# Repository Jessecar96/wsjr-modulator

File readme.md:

# The Weather STAR Revamped

This project is an update to https://github.com/thetechknight/wsjr-modulator that replaces the Arduino Mega, with a Reaspberry Pi Zero. This allows you to write a data sending solution on device instead of requiring a connection to another computer or server for data.

The `schematic` folder contains the updated schematic and board layout files in KiCad 8. 
`schematic_orig` contains thetechknight's original EAGLE cad schematic.
`code` contains code written for the Arduino based board written for  BASCOM-AVR.

The software that runs on the Raspberry Pi can be found here: https://github.com/Jessecar96/wsjr-data-encoder

License: https://creativecommons.org/licenses/by-nc-sa/4.0/

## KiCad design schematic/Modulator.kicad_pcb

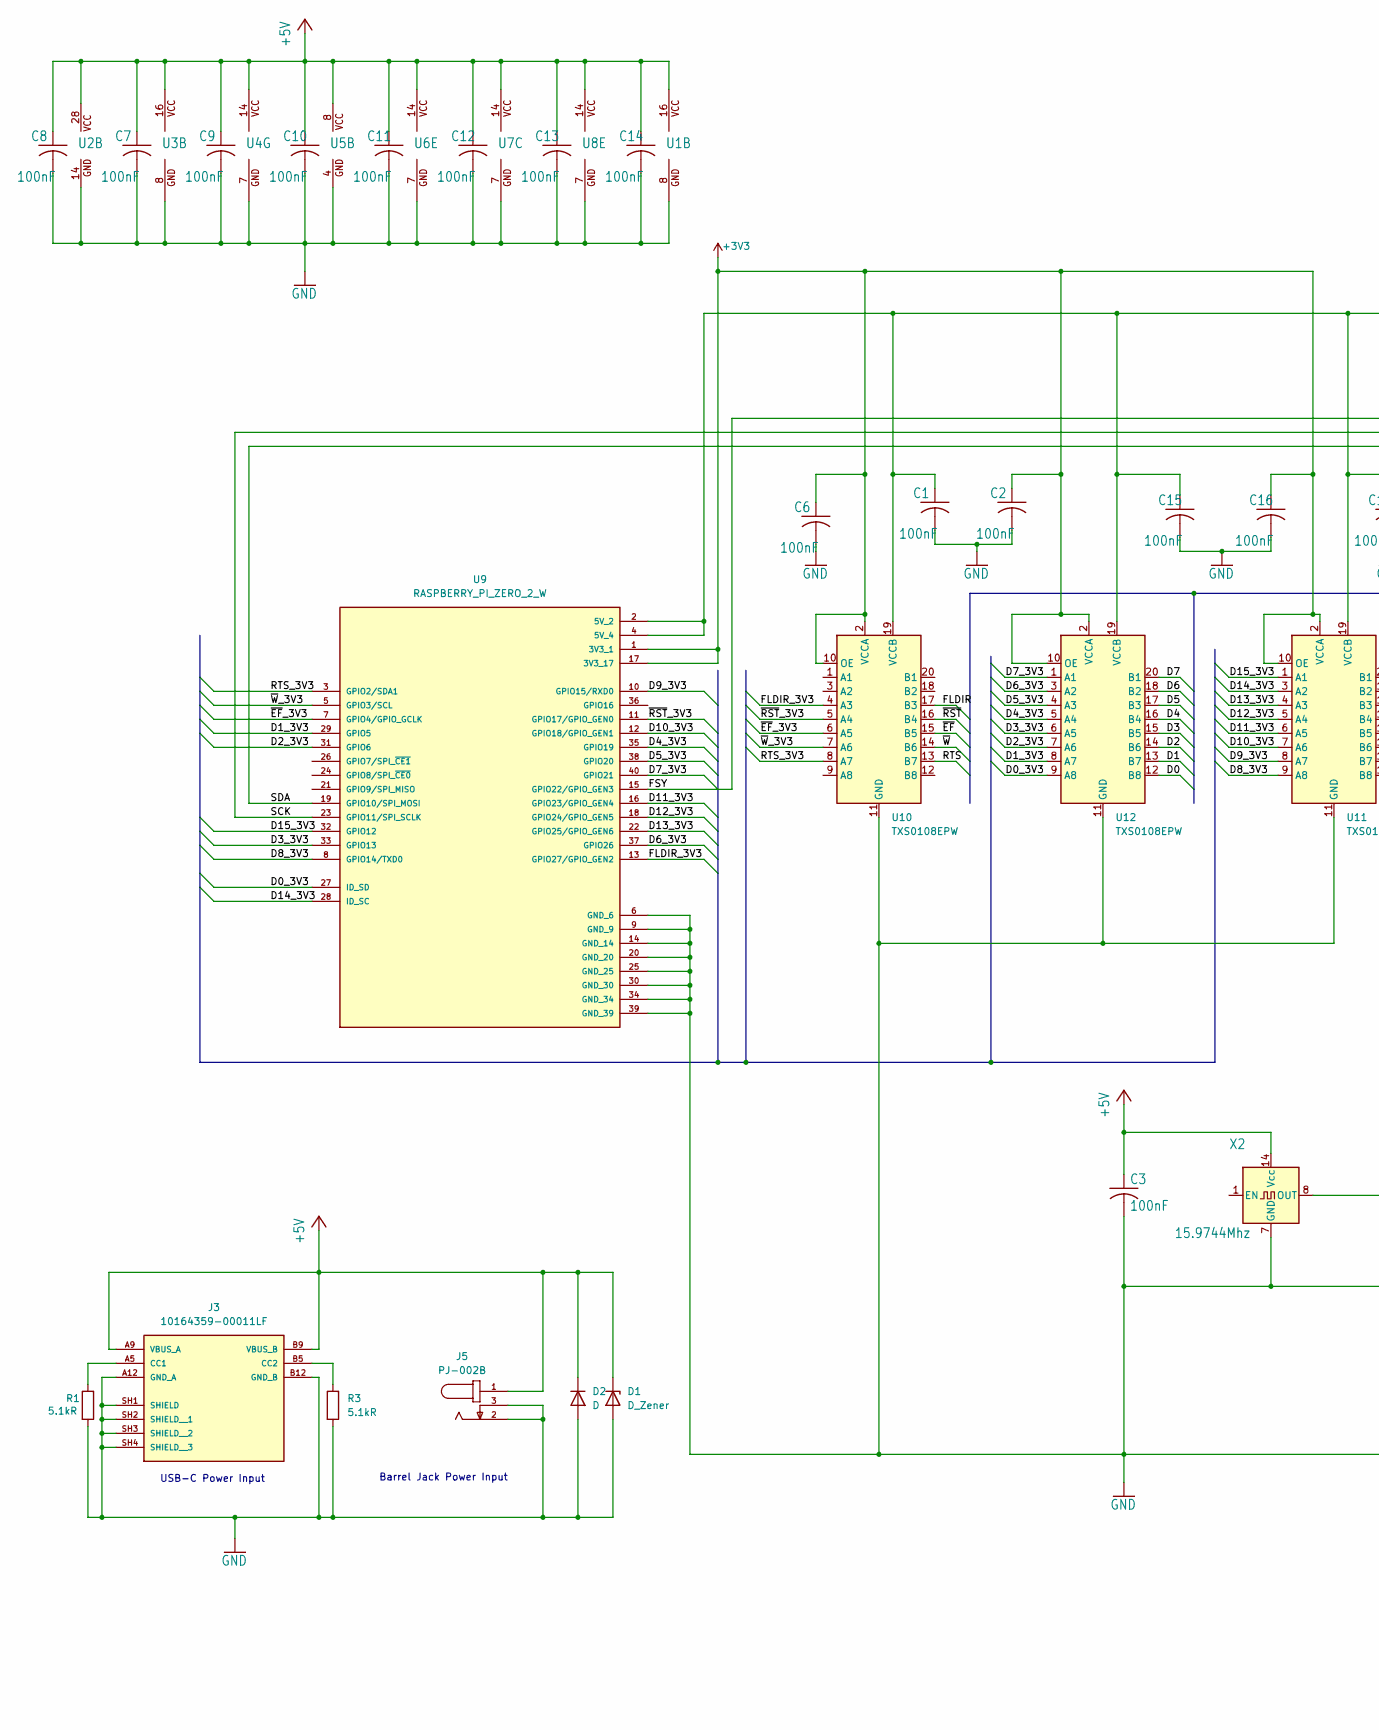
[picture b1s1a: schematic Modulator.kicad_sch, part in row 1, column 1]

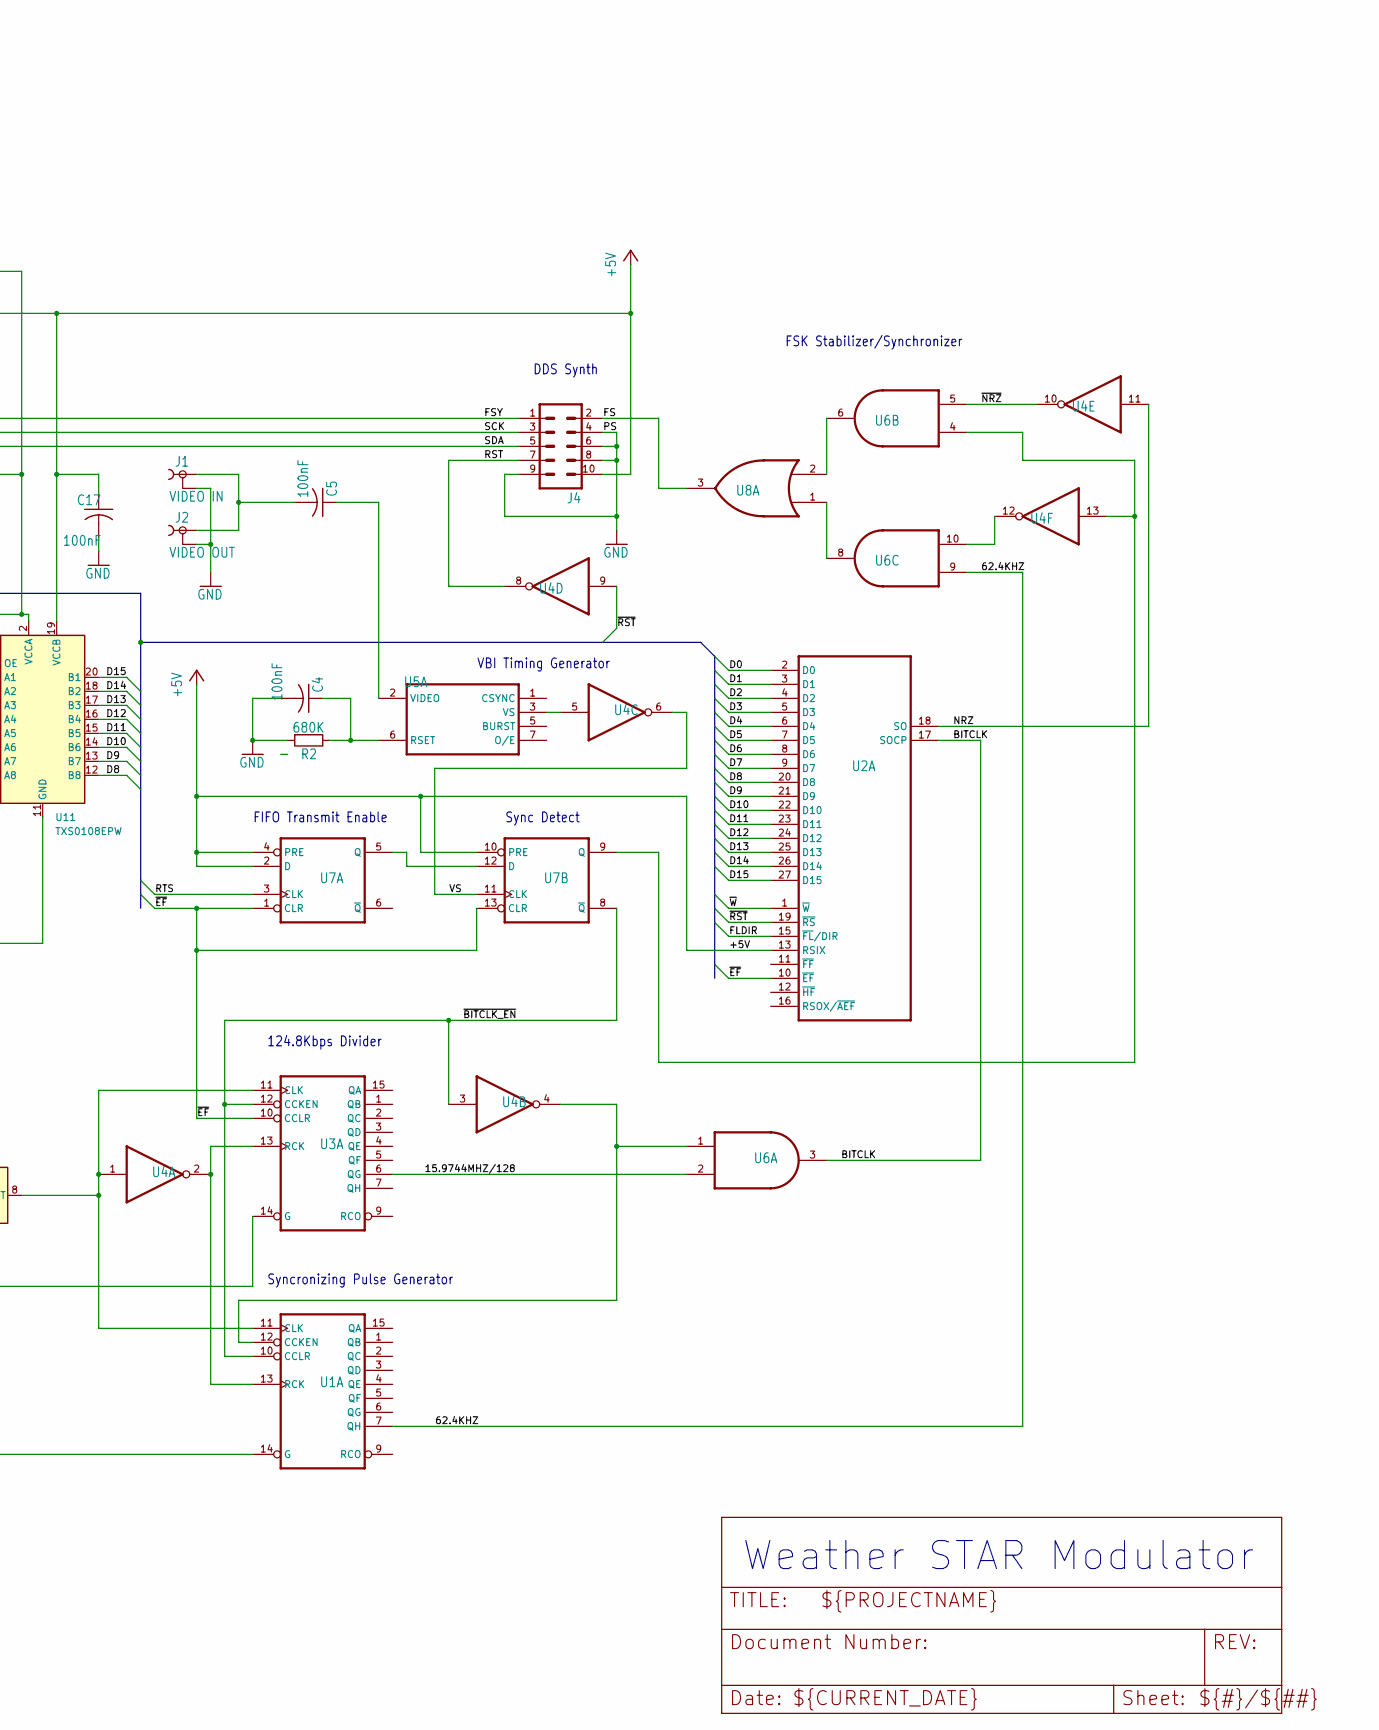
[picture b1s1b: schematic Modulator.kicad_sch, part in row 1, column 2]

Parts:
C1, C2, C6, C15, C16, C17: 100nF; C_0805_2012Metric_Pad1.18x1.45mm_HandSolder
C3, C4, C5, C7, C8, C9, C10, C11, C12, C13, C14: 100nF; C_Disc_D4.7mm_W2.5mm_P5.00mm
D1: D_Zener; D_DO-41_SOD81_P7.62mm_Horizontal
D2: D; D_DO-41_SOD81_P7.62mm_Horizontal
J1: VIDEO IN; TOBU3
J2: VIDEO OUT; TOBU3
J3: 10164359-00011LF; AMPHENOL_10164359-00011LF; PARTREV A
J4: MA05-2; AD9834
J5: PJ-002B; CUI_PJ-002B
R1, R3: 5.1kR; R_0805_2012Metric_Pad1.20x1.40mm_HandSolder
R2: 680K; R_Axial_DIN0207_L6.3mm_D2.5mm_P10.16mm_Horizontal
U1, U3: 74590N; DIL16
U2: IDT72125; DIP-28_W7.62mm_LongPads
U4: 7404N; DIL14
U5: LM1881N; DIL08
U6: 7408N; DIL14
U7: 7474N; DIL14
U8: 7432N; DIL14
U9: RASPBERRY_PI_ZERO_2_W; MODULE_RASPBERRY_PI_ZERO_2_W; PARTREV April 2024
U10, U11, U12: TXS0108EPW; TSSOP-20_4.4x6.5mm_P0.65mm
X2: 15.9744Mhz; Oscillator_DIP-14

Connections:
+3V3: C2.1, C6.1, C16.1, U9.1 (3V3_1), U9.17 (3V3_17), U10.2 (VCCA), U10.10 (OE), U11.2 (VCCA), U11.10 (OE), U12.2 (VCCA), U12.10 (OE)
+5V: C1.1, C3.1, C7.1, C8.1, C9.1, C10.1, C11.1, C12.1, C13.1, C14.1, C15.1, C17.1, D1.1 (K), D2.1 (K), J3.A9 (VBUS_A), J3.B9 (VBUS_B), J4.10, J5.1, U1.16 (VCC), U2.13 (RSIX), U2.28 (VCC), U3.16 (VCC), U4.14 (VCC), U5.8 (VCC), U6.14 (VCC), U7.2 (D), U7.4 (PRE), U7.10 (PRE), U7.14 (VCC), U8.14 (VCC), U9.2 (5V_2), U9.4 (5V_4), U10.19 (VCCB), U11.19 (VCCB), U12.19 (VCCB), X2.14 (Vcc)
/15.9744MHZ/128: U3.6 (QG), U6.2 (I1)
/62.4KHZ: U1.7 (QH), U6.9 (I0)
/BITCLK: U2.17 (SOCP), U6.3 (O)
/D0: U2.2 (D0), U12.12 (B8)
/D0_3V3: U9.27 (ID_SD), U12.9 (A8)
/D1: U2.3 (D1), U12.13 (B7)
/D1_3V3: U9.29 (GPIO5), U12.8 (A7)
/D2: U2.4 (D2), U12.14 (B6)
/D2_3V3: U9.31 (GPIO6), U12.7 (A6)
/D3: U2.5 (D3), U12.15 (B5)
/D3_3V3: U9.33 (GPIO13), U12.6 (A5)
/D4: U2.6 (D4), U12.16 (B4)
/D4_3V3: U9.35 (GPIO19), U12.5 (A4)
/D5: U2.7 (D5), U12.17 (B3)
/D5_3V3: U9.38 (GPIO20), U12.4 (A3)
/D6: U2.8 (D6), U12.18 (B2)
/D6_3V3: U9.37 (GPIO26), U12.3 (A2)
/D7: U2.9 (D7), U12.20 (B1)
/D7_3V3: U9.40 (GPIO21), U12.1 (A1)
/D8: U2.20 (D8), U11.12 (B8)
/D8_3V3: U9.8 (GPIO14/TXD0), U11.9 (A8)
/D9: U2.21 (D9), U11.13 (B7)
/D9_3V3: U9.10 (GPIO15/RXD0), U11.8 (A7)
/D10: U2.22 (D10), U11.14 (B6)
/D10_3V3: U9.12 (GPIO18/GPIO_GEN1), U11.7 (A6)
/D11: U2.23 (D11), U11.15 (B5)
/D11_3V3: U9.16 (GPIO23/GPIO_GEN4), U11.6 (A5)
/D12: U2.24 (D12), U11.16 (B4)
/D12_3V3: U9.18 (GPIO24/GPIO_GEN5), U11.5 (A4)
/D13: U2.25 (D13), U11.17 (B3)
/D13_3V3: U9.22 (GPIO25/GPIO_GEN6), U11.4 (A3)
/D14: U2.26 (D14), U11.18 (B2)
/D14_3V3: U9.28 (ID_SC), U11.3 (A2)
/D15: U2.27 (D15), U11.20 (B1)
/D15_3V3: U9.32 (GPIO12), U11.1 (A1)
/FLDIR: U2.15 (~FL/DIR), U10.17 (B3)
/FLDIR_3V3: U9.13 (GPIO27/GPIO_GEN2), U10.4 (A3)
/FS: J4.2, U8.3 (O)
/FSY: J4.1, U9.15 (GPIO22/GPIO_GEN3)
/NRZ: U2.18 (SO), U4.11 (I)
/RST: J4.7, U4.8 (O)
/RTS: U7.3 (CLK), U10.13 (B7)
/RTS_3V3: U9.3 (GPIO2/SDA1), U10.8 (A7)
/SCK: J4.3, U9.23 (GPIO11/SPI_SCLK)
/SDA: J4.5, U9.19 (GPIO10/SPI_MOSI)
/VS: U4.6 (O), U7.11 (CLK)
/~BITCLK_EN: U1.10 (CCLR), U3.12 (CCKEN), U4.3 (I), U7.8 (~Q)
/~EF: U2.10 (~EF), U3.10 (CCLR), U7.1 (CLR), U7.13 (CLR), U10.15 (B5)
/~EF_3V3: U9.7 (GPIO4/GPIO_GCLK), U10.6 (A5)
/~NRZ: U4.10 (O), U6.5 (I1)
/~RST: U2.19 (~RS), U4.9 (I), U10.16 (B4)
/~RST_3V3: U9.11 (GPIO17/GPIO_GEN0), U10.5 (A4)
/~W: U2.1 (~W), U10.14 (B6)
/~W_3V3: U9.5 (GPIO3/SCL), U10.7 (A6)
GND: C1.2, C2.2, C3.2, C4.2, C6.2, C7.2, C8.2, C9.2, C10.2, C11.2, C12.2, C13.2, C14.2, C15.2, C16.2, C17.2, D1.2 (A), D2.2 (A), J1.2, J1.2@1 (2), J1.2@2 (2), J2.2, J2.2@1 (2), J2.2@2 (2), J3.A12 (GND_A), J3.B12 (GND_B), J3.SH1 (SHIELD), J3.SH2 (SHIELD__1), J3.SH3 (SHIELD__2), J3.SH4 (SHIELD__3), J4.4, J4.6, J4.8, J4.9, J5.2, J5.3, R1.2, R2.2, R3.2, U1.8 (GND), U1.14 (G), U2.14 (GND), U3.8 (GND), U3.14 (G), U4.7 (GND), U5.4 (GND), U6.7 (GND), U7.7 (GND), U8.7 (GND), U9.6 (GND_6), U9.9 (GND_9), U9.14 (GND_14), U9.20 (GND_20), U9.25 (GND_25), U9.30 (GND_30), U9.34 (GND_34), U9.39 (GND_39), U10.11 (GND), U11.11 (GND), U12.11 (GND), X2.7 (GND)
unnamed: C5.2, J1.1, J2.1
unnamed: J3.A5 (CC1), R1.1
unnamed: J3.B5 (CC2), R3.1
unnamed: U1.12 (CCKEN), U4.4 (O), U6.1 (I0)
unnamed: U1.11 (CLK), U3.11 (CLK), U4.1 (I), X2.8 (OUT)
unnamed: U1.13 (RCK), U3.13 (RCK), U4.2 (O)
unnamed: U4.5 (I), U5.3 (VS)
unnamed: U4.13 (I), U6.4 (I0), U7.9 (Q)
unnamed: U4.12 (O), U6.10 (I1)
unnamed: C4.1, R2.1, U5.6 (RSET)
unnamed: C5.1, U5.2 (VIDEO)
unnamed: U6.6 (O), U8.2 (I1)
unnamed: U6.8 (O), U8.1 (I0)
unnamed: U7.5 (Q), U7.12 (D)

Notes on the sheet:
DDS Synth
VBI Timing Generator
USB-C Power Input
FSK Stabilizer/Synchronizer
Weather STAR Modulator
FIFO Transmit Enable
Sync Detect
Barrel Jack Power Input
124.8Kbps Divider
Syncronizing Pulse Generator

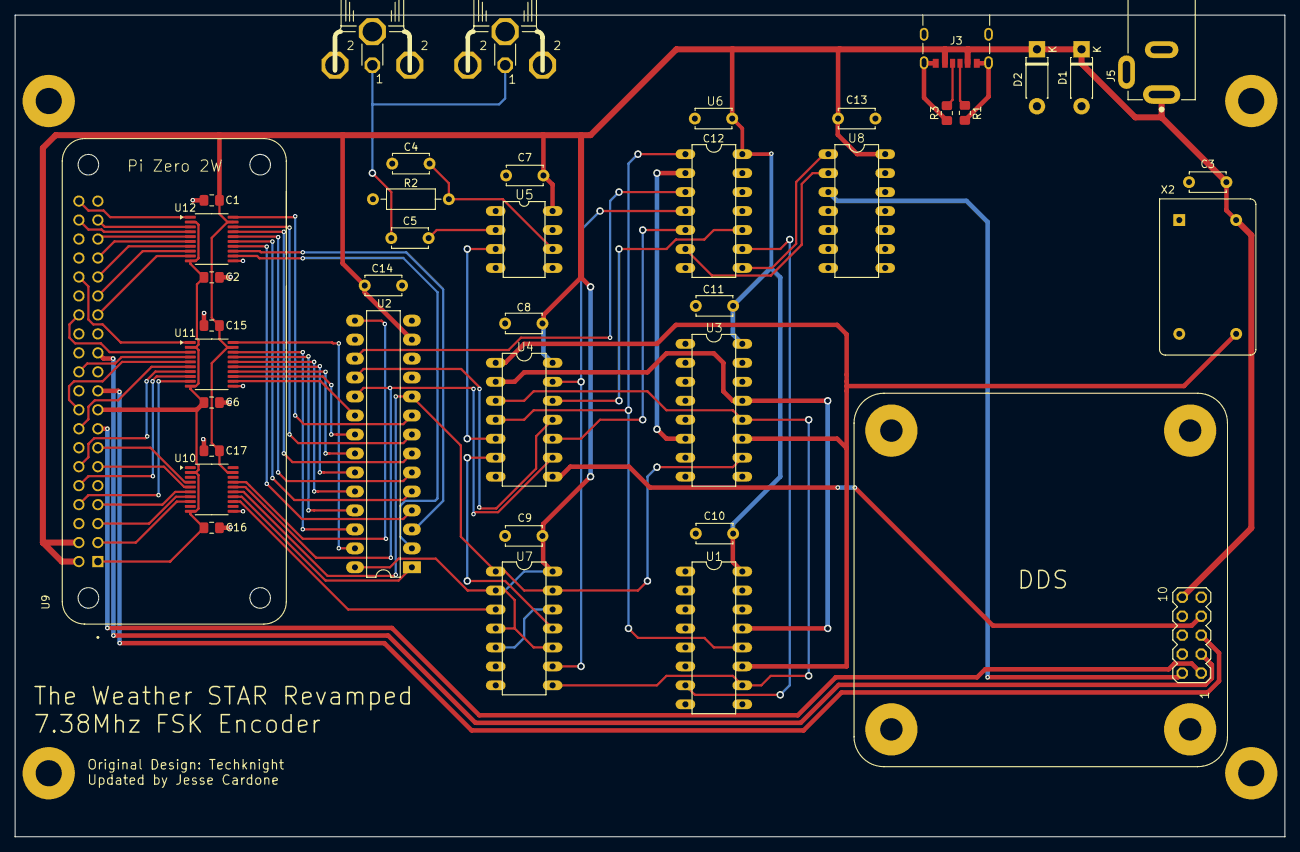
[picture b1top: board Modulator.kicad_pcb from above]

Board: 2 copper layers, 170.0 x 110.0 mm, 40 parts (0 on the bottom side), 71 nets.

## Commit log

2024-10-31 Add board layout
2024-10-31 Added images
2024-12-17 First draft of new circuit with raspberry pi
2024-12-17 Fix ground on top of bus
2024-12-20 First draft of PCB routing
2024-12-20 Make room for SMA connectors on DDS board
2024-12-21 Add decoupling capacitors to level shifters
2024-12-22 Change some decoupling capacitors, and usb-c resistors to SMT
2024-12-22 Update capacitor footprints
2024-12-22 Slight cleanup
2024-12-23 Add holes for case
2024-12-31 Update label placement
2024-12-31 Fix another label placement
2025-12-04 Add link to software source
